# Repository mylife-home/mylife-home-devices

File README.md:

# mylife-home-devices
MyLife Home devices

- [ePanel IO](epanel-io/README.md) :white_check_mark: Module de tableau électrique pour interconnecter E/S avec domotique (rpi/esp)
- [ePanel Energy Monitor](epanel-energy-monitor/README.md) :white_check_mark: Module de tableau électrique pour mesurer la consommation électrique
- [ePanel Controller](epanel-controller/README.md) :white_check_mark: Module de tableau électrique pour contrôler IO et Energy Monitor
- [Garden box](garden-box/README.md) :white_check_mark: Boîtier de commandes/capteurs dans le jardin
- [RGB garden box](rgb-garden-box/README.md) :white_check_mark: Boîtier de commande spots RGB dans le jardin
- [RGB spot 10W](rgb-spot-10w/README.md) :white_check_mark: Reprise de spots existant infrarouge pour connexion direct cables RGB
- [Garage door driver](garage-door-driver/README.md) :white_check_mark: Pilote de porte de garage
- [Clim driver](clim-driver/README.md) :white_check_mark: Pilote de clim
- [Gate driver](gate-driver/README.md) :hourglass: Pilote de portail
- [Bed Smart Plug](bed-smart-plug/README.md) :white_check_mark: "Multiprise intelligente" pour mettre en tête de lit
- [Presence Wifi sensor](presence-wifi-sensor/README.md) :question: Détecteur de présence Wifi
- [RGB LED inverter](rgb-led-inverter/README.md) :no_entry: common anode -> common cathode
- RGB indoor box :question: Boîtier de commande spots/ruban leds RGB en intérieur
- Kitchen hood driver :question: Pilote de hôte
- [Pergola driver](pergola-driver/README.md) :question: Pilote de pergola
- [Fairy lights](fairy-lights/README.md): :white_check_mark: guirlande de noël
- [Heater driver](heater-driver/README.md): :question: pilote de radiateur
- [Deco light](deco-light/README.md): :question: Lumière de décoration

## Notes
- Tutorial KiCad: https://www.youtube.com/playlist?list=PLuQznwVAhY2WA4CIf3_aB_e8hRCSbQuUp
- Best practice routing PCB: https://resources.altium.com/fr/p/top-5-pcb-design-guidelines-every-pcb-designer-needs-know
- Kicad to JLCPCB
  - https://support.jlcpcb.com/article/149-how-to-generate-gerber-and-drill-files-in-kicad
  - https://support.jlcpcb.com/article/84-how-to-generate-the-bom-and-centroid-file-from-kicad
  - plugin pour aide a la generation de commande : https://github.com/Bouni/kicad-jlcpcb-tools
  - plugin pour importer les composants JLCPCB dans Kicad : https://github.com/TousstNicolas/JLC2KiCad_lib
- Component footprints : https://componentsearchengine.com/
- ESP32-POE:
  - NE PAS utiliser GPIO0 si possible (ne pas le mettre DOWN au boot)
  - Attention : Version avec antenne interne est plus grande (pas que l'ESP, toute la board). Le footprint Kicad courant correspond à la version avec antenne externe : 
- ESP8266 strapping pins:
  - GPIO0, GPIO1, GPIO2: boot failure if pulled LOW
  - GPIO15: boot failure if pulled HIGH
  - GPIO1, GPIO2, GPIO3, GPIO9, GPIO10, GPIO16: pin is high at BOOT

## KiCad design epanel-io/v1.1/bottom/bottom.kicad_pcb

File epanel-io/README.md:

# ePanel IO

## Besoin

- 20 IO au moins
- mettre un Switch ou jumper pour relier les phases et neutres de 2 entrées sorties voisines (pour pouvoir relier ensemble ceux qui viennent du même disjoncteur)

- IO / disjoncteurs:
  - R1: 7 + 3 extension + escalier
  - RDC: 5 + porche
  - Dehors: terrasse (vers spa)

## Design

- Rpi pico: 2 modules with 10 I/O each with io port0 = Zc + power supply
- Rpi pico + esp : jumper pour alim séparée => permet live debug usb + reboot ?
- Borniers "détachables" ?
- Noter sur le silkscreen a quoi correspondent les borniers/pin headers/jumpers
- Grouper les IO 4 par 4 (1 phase et 1 neutre pour 4 IO) => 4 + 4 + 2 par RPI

### Materiel

- Boîtier : https://fr.rs-online.com/web/p/boitiers-rail-din/7495837
- Borniers :
  - 2 contacts : https://fr.rs-online.com/web/p/borniers-pour-circuits-imprimes/1444286
  - 3 contacts : https://fr.rs-online.com/web/p/borniers-pour-circuits-imprimes/1444293

---

- Découpage IO:
  - R1: 11     => 4 + 4 + 4
  - RDC: 6     => 4 + 2
  - Dehors: 1  => 2
=> 2x 4+4+2 OK

### ePanel (common with energy monitor)

- i2c bus
- Connexion i2c + power
- master controler olimex esp32 dans le tableau electrique

## V1.1

### Materiel :

- Boitier aéré :
  - CNMB/6V/2 https://fr.rs-online.com/web/p/boitiers-rail-din/7495913
  - CNMB/6V/KIT https://fr.rs-online.com/web/p/boitiers-rail-din/7495840
- Borniers enfichables :
  - Bornier 3 voies : https://fr.farnell.com/phoenix-contact/1792252/fiche-male-90deg-ci-3v-5-08mm/dp/3705456
  - Base 3 voies : https://fr.farnell.com/en-FR/phoenix-contact/mstb-2-5-3-g-5-08/terminal-block-header-3pos-r-a/dp/2671262
  - Bornier 5 voies : https://fr.farnell.com/phoenix-contact/1792278/fiche-male-90deg-ci-5v-5-08mm/dp/3705470
  - Base 5 voies : https://fr.farnell.com/phoenix-contact/1759046/bornier-header-5-voies-90-traversant/dp/2671264

### Observations V1 19 Juillet 2025 sur V1

**Très chauds :**
- R2 - R3
- U2

**Chauds (tout le haut) :**
- U4 R7 et toute la ligne
- R36 diode 1N4007 et toute la ligne

## V1

_Mise en service : 8 OCT 2022_

### Wiring

IO from left to right:  
0,1,2,3, 8,9, 4,5,6,7  
_ZC sur 8,9_

### Top

### Bottom

### Images

#### Fabrication

- enlever les renforts au milieu a la pince + finition dremel
- raboter les cales pour la carte superieure au dremel
- souder les pin headers
- souder les borniers
- couper a la pince les pins qui depassent des soudures de borniers qui empechent de fermer le boitier correctement

_Après fix (Q3/Q4 et Q5/Q6 etaient morts)_

#### Installation

_Ancienne domotique_

_Nouvelle domotique_

## Prototype-1

### Tests

- Code:
  - https://github.com/vincent-tr/pico-experiments/tree/main/zc
  - https://github.com/vincent-tr/pico-experiments/tree/main/triac
  - https://github.com/vincent-tr/pico-experiments/tree/main/mosfet
- Images:
  <br/>

### Observations

- Trous pour borniers trop gros
- Triac:
  - fait clignoter un spot led 10w en OFF
  - fait un leger bruit sur passage de OFF a ON
  - dimming: fait un bourdonnement marqué avec spot 35W (testé à 50/255 et 150/255)
- Mosfet:
  - fait clignoter un spot led 10w en OFF
  - avec resistances 100k en // de la charge, pareil
  - avec spot 35W, R5 brule
  - après avoir changé alim par HLK-PM12, c'est OK!

## Prototype-2

### Tests
- Code:
  - https://github.com/vincent-tr/pico-experiments/tree/main/mosfet
- Images:
  <br/>

### Observations

- Montage faux : j'ai dessoudé la diode D3 et connecté son anode au neutral
- Anoter les IO (dominos/pin headers) sinon c'est difficile a retrouver après
- La taille du PCB correspond parfaitement au boitier DIN : CNMB/4/kit
- Montage fonctionne avec spot 35w + sport réel salon (mais pas avec spot test 10w, que on/off, non dimmable?)
- Pas de chauffe
- pico "RUN" pin si utilisé sur breadboard doit être relié au VCC, sinon le laisser dangling peut causer des reboot intempestifs

## Prototype-3

### Tests

- Images:
  <br/>

## Notes

### Mosfet dimmer schematics

- [Prototype1 (does not work)](mosfet-dimmer.png)
- https://electronics.stackexchange.com/questions/557763/trailing-edge-dimmer-circuit-limitations
- https://sound-au.com/project157.htm
- https://electronics.stackexchange.com/questions/277884/problems-with-a-back-to-back-mosfet-dimmer-for-230vac
- IRF740 -> 10A

### 220v current sensor (input)

- https://arduino.stackexchange.com/questions/37044/127v-220v-ac-sensor-whats-the-role-of-this-particular-resistor
- https://smartsolutions4home.com/detecting-mains-voltage-with-microcontroller/
- https://bytesofgigabytes.com/embedded/sensing-ac-voltage-using-microcontroller/
- Zc : https://electronics.stackexchange.com/questions/215094/how-to-test-if-zero-crossing-is-working

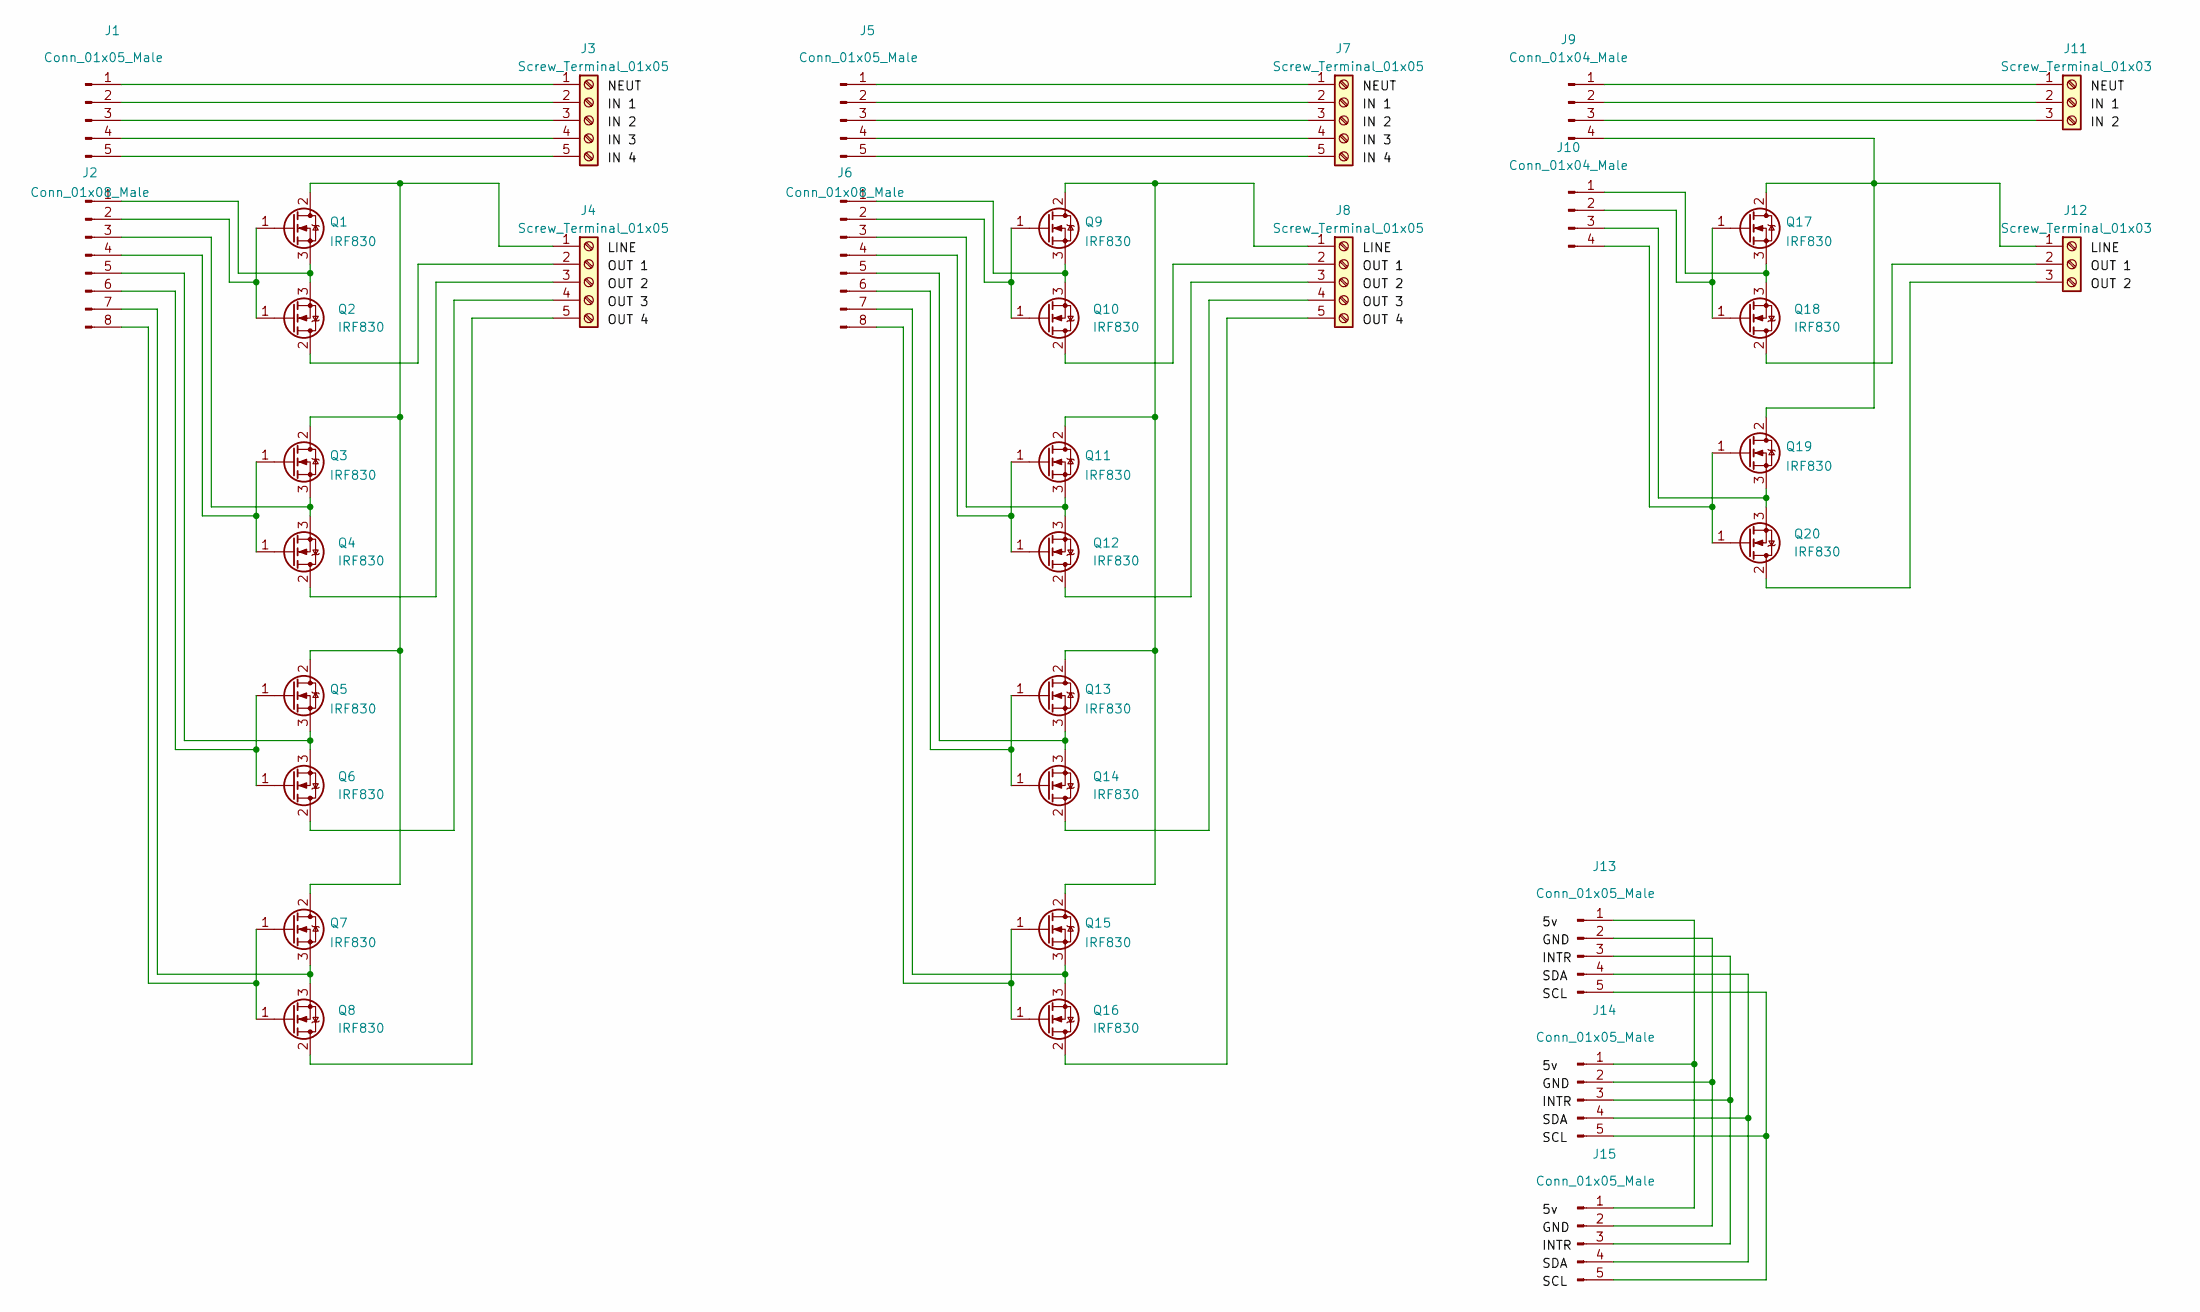
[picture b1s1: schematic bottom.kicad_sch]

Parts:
J1, J5, J13, J14, J15: Conn_01x05_Male; PinHeader_1x05_P2.54mm_Vertical
J2, J6: Conn_01x08_Male; PinHeader_1x08_P2.54mm_Vertical
J3, J4, J7, J8: Screw_Terminal_01x05; TerminalBlock_bornier-5_P5.08mm
J9, J10: Conn_01x04_Male; PinHeader_1x04_P2.54mm_Vertical
J11, J12: Screw_Terminal_01x03; TerminalBlock_bornier-3_P5.08mm
Q1, Q2, Q3, Q4, Q5, Q6, Q7, Q8, Q9, Q10, Q11, Q12, Q13, Q14, Q15, Q16, Q17, Q18, Q19, Q20: IRF830; TO-263-3_TabPin2; LCSC C693297

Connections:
unnamed: J1.1, J3.1
unnamed: J1.2, J3.2
unnamed: J1.3, J3.3
unnamed: J1.4, J3.4
unnamed: J1.5, J3.5
unnamed: J2.1, Q1.3 (S), Q2.3 (S)
unnamed: J2.2, Q1.1 (G), Q2.1 (G)
unnamed: J2.3, Q3.3 (S), Q4.3 (S)
unnamed: J2.4, Q3.1 (G), Q4.1 (G)
unnamed: J2.5, Q5.3 (S), Q6.3 (S)
unnamed: J2.6, Q5.1 (G), Q6.1 (G)
unnamed: J2.7, Q7.3 (S), Q8.3 (S)
unnamed: J2.8, Q7.1 (G), Q8.1 (G)
unnamed: J4.1, Q1.2 (D), Q3.2 (D), Q5.2 (D), Q7.2 (D)
unnamed: J4.2, Q2.2 (D)
unnamed: J4.3, Q4.2 (D)
unnamed: J4.4, Q6.2 (D)
unnamed: J4.5, Q8.2 (D)
unnamed: J5.1, J7.1
unnamed: J5.2, J7.2
unnamed: J5.3, J7.3
unnamed: J5.4, J7.4
unnamed: J5.5, J7.5
unnamed: J6.1, Q9.3 (S), Q10.3 (S)
unnamed: J6.2, Q9.1 (G), Q10.1 (G)
unnamed: J6.3, Q11.3 (S), Q12.3 (S)
unnamed: J6.4, Q11.1 (G), Q12.1 (G)
unnamed: J6.5, Q13.3 (S), Q14.3 (S)
unnamed: J6.6, Q13.1 (G), Q14.1 (G)
unnamed: J6.7, Q15.3 (S), Q16.3 (S)
unnamed: J6.8, Q15.1 (G), Q16.1 (G)
unnamed: J8.1, Q9.2 (D), Q11.2 (D), Q13.2 (D), Q15.2 (D)
unnamed: J8.2, Q10.2 (D)
unnamed: J8.3, Q12.2 (D)
unnamed: J8.4, Q14.2 (D)
unnamed: J8.5, Q16.2 (D)
unnamed: J10.1, Q17.3 (S), Q18.3 (S)
unnamed: J10.2, Q17.1 (G), Q18.1 (G)
unnamed: J10.3, Q19.3 (S), Q20.3 (S)
unnamed: J10.4, Q19.1 (G), Q20.1 (G)
unnamed: J9.1, J11.1
unnamed: J9.2, J11.2
unnamed: J9.3, J11.3
unnamed: J9.4, J12.1, Q17.2 (D), Q19.2 (D)
unnamed: J12.2, Q18.2 (D)
unnamed: J12.3, Q20.2 (D)
unnamed: J13.1, J14.1, J15.1
unnamed: J13.2, J14.2, J15.2
unnamed: J13.3, J14.3, J15.3
unnamed: J13.4, J14.4, J15.4
unnamed: J13.5, J14.5, J15.5

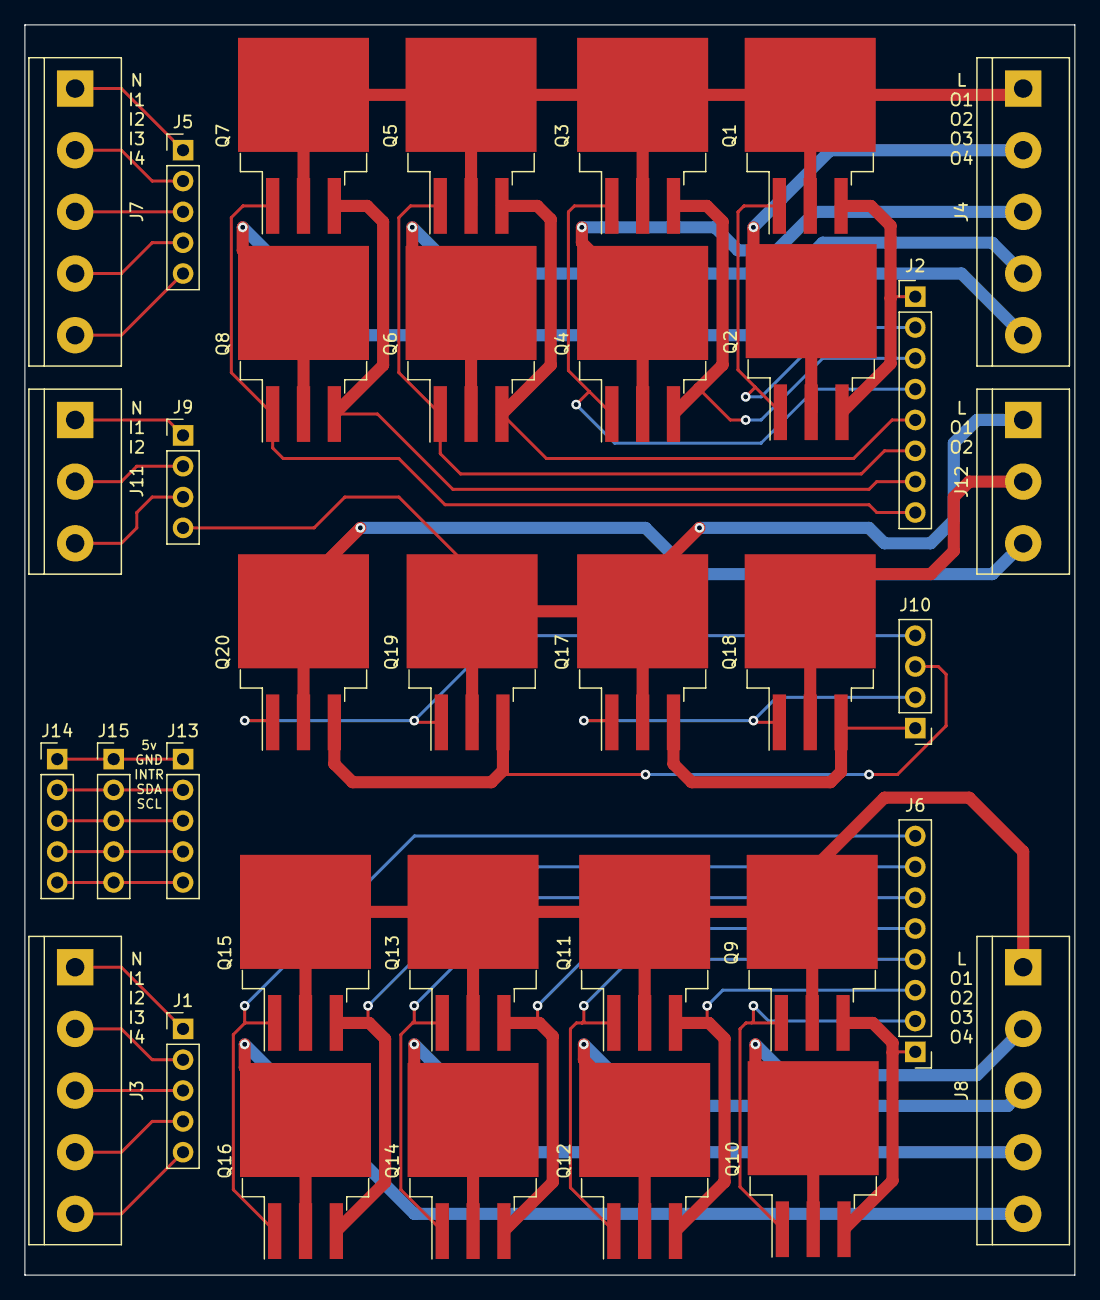
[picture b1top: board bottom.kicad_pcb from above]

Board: 2 copper layers, 86.5 x 103.0 mm, 35 parts (0 on the bottom side), 51 nets.

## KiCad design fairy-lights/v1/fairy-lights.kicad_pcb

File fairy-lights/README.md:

# Fairy lights

## Besoin

- Avec Eléonore
- Guirlande pour sapin
- Intégré ESPHome

## Design

- Guirlande :
  - WS2812B
  - https://amzn.eu/d/6PvWFXF
  - ( https://www.adafruit.com/product/4917 )
- Contrôleur :
  - WeMos D1 mini, sur gpio3 pour DMA
  - config esphome dma -> GPIO3 - RX
- Alimentation :
  - Puissance guirlande : Alim 5V 6A -> 60ma / led
  - ~alim 6A (69.5x39x24) : https://fr.rs-online.com/web/p/alimentations-a-decoupage/1358945~
  - ~alim 8A (87x52x29.5) : https://fr.rs-online.com/web/p/alimentations-a-decoupage/1358955~
  - alime externe 5V 8A : https://www.amazon.fr/dp/B088FBXTPS : `+` au milieu `-` à l'extérieur, 5.5mm - 2.5mm
  - Connecteur : 
    - https://fr.rs-online.com/web/p/connecteurs-d-alimentation-dc/2832406 - 283-2406
    - ( https://fr.rs-online.com/web/p/connecteurs-d-alimentation-dc/8782606 )
- IRLZ44N pour switch l'alim (sans heatsink), sortie esp direct sur Din LEDs : https://fr.rs-online.com/web/p/transistors-mosfet/5410086 541-0086
- Boitier : https://fr.rs-online.com/web/p/boitiers-pour-usage-general/9190373 - 919-0373

## V1

### Wiring

- `+` -> fil avec points noirs
- `D` -> fil du milieu
- `-` -> fil de l'autre côté 

### 3D view

### Main

### Images

## Prototype 1

- Sur breadboard
- Verifier qu'on peut piloter la guirlande avec esp8366/esphome

### Pinout de la guirlande

- `+` -> fil avec points noirs
- `D` -> fil du milieu
- `-` -> fil de l'autre côté

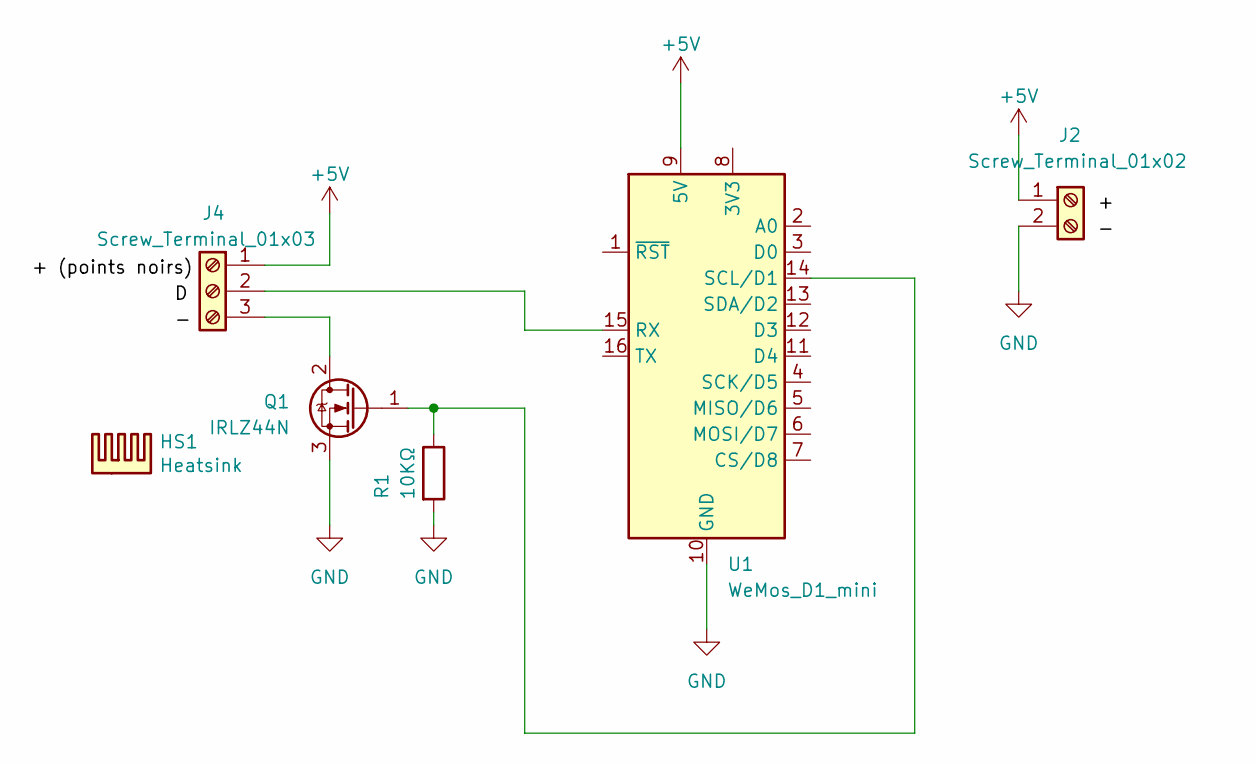
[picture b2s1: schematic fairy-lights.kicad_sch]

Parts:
HS1: Heatsink; Heatsink_Fischer_SK104-STC-STIC_35x13mm_2xDrill2.5mm
J2: Screw_Terminal_01x02; TerminalBlock_bornier-2_P5.08mm
J4: Screw_Terminal_01x03; TerminalBlock_bornier-3_P5.08mm
Q1: IRLZ44N; TO-220-3_Vertical
R1: 10KΩ; R_Axial_DIN0207_L6.3mm_D2.5mm_P15.24mm_Horizontal
U1: WeMos_D1_mini; WEMOS_D1_mini_light

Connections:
+5V: J2.1, J4.1, U1.9 (5V)
GND: J2.2, Q1.3 (S), R1.2, U1.10 (GND)
unnamed: J4.2, U1.15 (RX)
unnamed: J4.3, Q1.2 (D)
unnamed: Q1.1 (G), R1.1, U1.14 (SCL/D1)

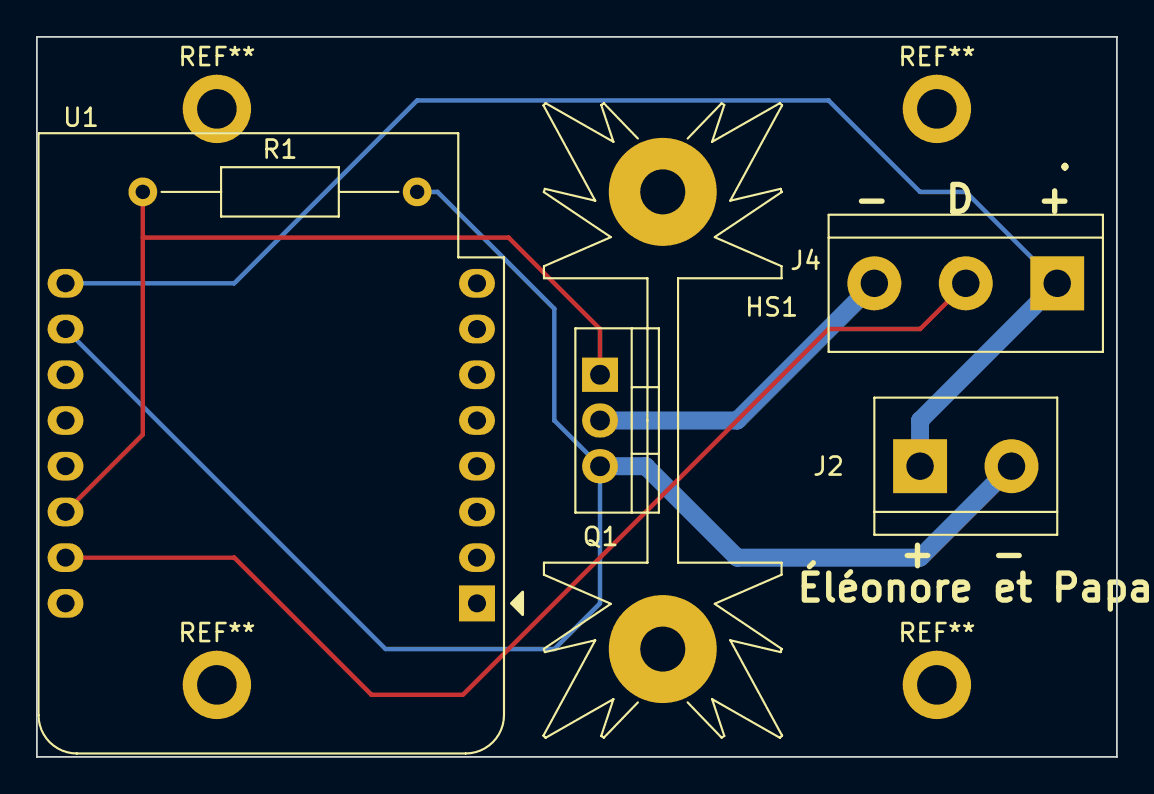
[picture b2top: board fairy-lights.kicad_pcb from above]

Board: 2 copper layers, 60.0 x 40.0 mm, 6 parts (0 on the bottom side), 5 nets.

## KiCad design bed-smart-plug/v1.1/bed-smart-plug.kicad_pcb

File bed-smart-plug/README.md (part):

# Bed Smart Plug

## Besoin

- Récepteur 433mhz (pour télécommande)
- Capteur température
- 4 sorties prises entre 5W et 200W
- Wifi et Ethernet
- Boitier :
  - peut etre relativement large/long, mais plat
  - avec les prises sur un côté
  - comme un switch
  - comme ca on peut le mettre sous un meuble, ou derriere un meuble debout

### Emplacements

- chambre parents
- chambre Eléonore
- chambre Éloïse
- chambre d'amis ?
- rdc derrière TV ?
- bibliothèque pour lampe pot de fleurs + température ?

## Choix techniques

- ESP32 ethernet ou wifi
  - prévoir des trous sur le PCB pour fixer l'esp avec un serre flex entre son header et son module ESP, sur l'inscription "ESP32-PoE"
- SSR pour éviter claquement relais
  - BT136 (4A max)
  - Dissipateurs
  - Fusible 5x20 à souder
- Entree Prise alim IEC C14
- Sorties prises IEC C13 pour avoir un format plus compact
- Capteur température :
  - DS18b20
  - avec Jack
  - possible souder jack a la main sinon
  - capteur integré inutile (mesure la temperature de l'esp/des triac pas de la piece)
- Télécommande 433MHz:
  - Renkforce 1208459
  - https://amzn.eu/d/fGBrWJP
  - https://www.conrad.fr/fr/p/renkforce-1208459-sans-fil-telecommande-interieure-1208459.html

## Design

- Board : ESP32-POE https://www.olimex.com/Products/IoT/ESP32/ESP32-POE/open-source-hardware
- Alim 220v -> 5V 1A : 
  - ~~https://fr.rs-online.com/web/p/alimentations-a-decoupage/1812200~~ (n'existe plus)
  - https://fr.rs-online.com/web/p/alimentations-a-decoupage/1359226
- Jack DS18B20 :
  - https://www.amazon.fr/dp/B075FYYLLV/
  - https://fr.rs-online.com/web/p/connecteurs-jacks/5051299
- Récepteur 433MHz : (modulation ASK)
  - ~~AM-RX12A-433P https://fr.farnell.com/rf-solutions/am-rx12a-433p/recepteur-module-rf-433-92-110dbm/dp/2759279~~ (frais de gestion trop chers)
  - QAM-RX10-433 https://fr.rs-online.com/web/p/modules-rf/1258208
  - pinout compatible
  - normalement 5V, tester en broadboard avec alim 5V + pont diviseur sur les data pour passer a 3.3V
- Triac : BT136-600E https://fr.rs-online.com/web/p/triac/7271120
  - ~~Dissipateur https://fr.rs-online.com/web/p/dissipateurs-de-chaleur/1898101/~~
  - moins haut, même base : https://fr.rs-online.com/web/p/dissipateurs-de-chaleur/1898094
  - vis M3 : même que garden box : https://fr.rs-online.com/web/p/vis-a-rondelle-indesserrable/0279149
  - écrous M3 : https://fr.rs-online.com/web/p/ecrous-hexagonaux/0560293
- Porte fusible : https://fr.rs-online.com/web/p/porte-fusibles/1769047
  - Fusible : https://fr.rs-online.com/web/p/fusibles-cartouches/6686007
- Boitier :
  - https://fr.rs-online.com/web/p/boitiers-pour-usage-general/8180494
    - noir comme les connecteurs C13/C14
    - les facades laterales sont d'un seul tenant: le couvercle est "plat", plus facile pour percer les facades.
  - Vis de fixation PCB : https://fr.rs-online.com/web/p/vis-autotaraudeuses/4831202
- Prises :
  - ~~entree C14 : https://fr.rs-online.com/web/p/connecteurs-iec/8117207~~
  - ~~sortie C13 : https://fr.rs-online.com/web/p/connecteurs-iec/8117193~~
  - sortie C13 x 4 à clip : https://fr.rs-online.com/web/p/connecteurs-iec/2318101
    - couper une barre (phase), laisser les 2 autres
    - montage :

  - entrée C13 à clip : https://fr.rs-online.com/web/p/connecteurs-iec/0481623
    - montage :

  - ~~1 entrée 4 sorties : https://fr.rs-online.com/web/p/connecteurs-iec/3135474~~
    - semble indisponible

  - Prise C14 pour câbles : https://amzn.eu/d/47d2yMY

## Observations Prototype-1 epanel-io

- cf [epanel-io/README.md#observations](../epanel-io/README.md#observations) - Triac
- si on enleve snubber du phototriac, toujours une fuite (couper la piste entre C3 et C4)
- si on enleve les 2 snubbers, plus de fuite, spot led 10w reste eteint (couper la piste entre C3 et le triac)

## Prototype-1

### Objectifs

- Triac: 
  - dissipateurs
  - snubbers/bruit/fuite
    - spot 10w
    - guirlande boules
    - lampe bureau
    - lampe chevet
    - alim a decoupage
- 433MHz receiver
  - binding avec telecommandes
- ds18b20
  - jack pinout: voir quelles broches sur chaque prise matchent + selectionner le pinout qu'on veut.
- fusibles

### Schematic

- [Schematic](prototype-1/schematic.png)

### Pinout

- GPIO02 : Triac
- GPIO13 : DS18B20
- GPIO36 : Récepteur 433MHz

### Observations

- Dissipateur :
  - Rapprocher dissipateur et triac de 0.5 - 1 mm
  - Fixation dissipateur/triac : écrou M3 + reprendre vis M3 anti-deserrage garden-box
- Fusibles : OK
- Triac :
  - spot 10w :
    - triac snubber => fuite (KO)
    - opto snubber => fuite (KO)
    - sans snubber => pas de bruit (OK)
  - Perceuse à colonne :
    - puissance : 1.6A au démarrage puis 0.8
    - Avec/Sans snubber : pas de bruit mais la perceuse fait elle du bruit
    - apres 5 mins dissipateur + triac froids 
  - Lampe chevet Éloïse
    - puissance : 26.5ma
    - Avec snubber : KO bruit quand off
    - Sans snubber : OK sans bruit
  - Guirlande Éloïse
    - Avec snubber : KO clignote
    - Sans snubber : OK sans bruit
    - puissance très instable semble avec des pics a 600ma puis revient a 0ma (problème multimètre ?)
  - Lampe bureau
    - puissance semble 25ma (problème multimètre ?)
    - Avec snubber : KO bruit quand off
    - Sans snubber : OK sans bruit
  - Lampe chevet Eléonore
    - puissance 1.5a???? (problème multimètre ?) -> Ampoule à incandescence 40W
    - Avec snubber : OK sans bruit
    - Sans snubber : OK sans bruit
- Prise jack 

  (de gauche à droite) 
  - 1 : corps
  - 2 : pin penché 
  - 3 : base pin central
  - 4 : extrémité pin central

  Attention : bien enfoncer la prise
  - On peut mettre la prise sous l'ESP

- Récepteur 433mhz
  - Les 2 pins data sont reliés ensemble 
  - Connecter au 5V, et mettre un point diviseur :
    - R1 = 10k (entre output recepteur et input ESP)
    - R2 = 2x 10k en série (entre input ESP et GND)
  - Config dump : 
```yaml
    remote_receiver:
      pin: GPIO36
      dump:
      - rc_switch
      tolerance: 50%
      filter: 250us
      idle: 4ms
      buffer_size: 2kb
```
  - Valeurs (le repeat est très rapproché) : 
    - `Received RCSwitch Raw: protocol=1 data='...'`
  
  _Config télécommande grise : 1 = ON, 5 = ON_
  
| Action | code télécommande | code ABCD | ?? | on/off |
|---|---|---|---|---|
| A on   | 00 01 01 01 00 | 00 01 01 01 | 01 | 00 01 |
| A off  | 00 01 01 01 00 | 00 01 01 01 | 01 | 01 00 |
| B on   | 00 01 01 01 00 | 01 00 01 01 | 01 | 00 01 |
| B off  | 00 01 01 01 00 | 01 00 01 01 | 01 | 01 00 |
| C on   | 00 01 01 01 00 | 01 01 00 01 | 01 | 00 01 |
| C off  | 00 01 01 01 00 | 01 01 00 01 | 01 | 01 00 |
| D on   | 00 01 01 01 00 | 01 01 01 00 | 01 | 00 01 |
| D off  | 00 01 01 01 00 | 01 01 01 00 | 01 | 01 00 |

  _Config télécommande blanche : 1 = ON, 2 = ON_

  => Code télécommande : `00 00 01 01 01`, le reste semble correspondre

  - Avec récepteur dans salon :
    - Fontionne depuis CH1
    - Fonctionne depuis CHP

  _Config télécommande renkforce : pos 1_

| Action | code télécommande | code ABCD | ?? | on/off |
|---|---|---|---|---|
| 1 on   | 00 01 01 01 | 00 01 01 01 01 | 01 | 01 01 |
| 1 off  | 00 01 01 01 | 00 01 01 01 01 | 01 | 01 00 |
| 2 on   | 00 01 01 01 | 01 00 01 01 01 | 01 | 01 01 |
| 2 off  | 00 01 01 01 | 01 00 01 01 01 | 01 | 01 00 |
| 3 on   | 00 01 01 01 | 01 01 00 01 01 | 01 | 01 01 |
| 3 off  | 00 01 01 01 | 01 01 00 01 01 | 01 | 01 00 |
| 4 on   | 00 01 01 01 | 01 01 01 00 01 | 01 | 01 01 |
| 4 off  | 00 01 01 01 | 01 01 01 00 01 | 01 | 01 00 |

## Prototype-2

### Objectifs

- boitier 
- sortie RJ45
- sortie prise jack
- fixations C13/C14
- tester nouveau dissipateur

### Observations

- Dissipateur + écrou de fixation OK
- Boîtier :
  - pas assez long (on ne peut pas mettre toutes les prises + ESP)
  - pas assez large (ESP ne tient pas en largeur)
  - hauteur OK mais prise C14 avec vis sur les côtés ne tient pas en hauteur : voir pour prendre une encastrable comme la multiprise C13
  - aluminium pour ne pas se déformer avec les trous ?
  - aérations ?
  - **aluminium trop cher, autres boitiers mauvaise taille. On garde celui là mais en mettant l'alime/jack/rj45 sur un côté**
- Multiprise C13 x4 : séparation des phases OK

- Perçage boitier pour multiprise C13x4
  - Tracer au cutter + règle métallique
  - Le gros :
    - Découpage disque Dremel vitesse 5 + coins avec perceuse a colonne plus gros forêt placo (faire coins en premier)
  - la finition :
    - tubes ponceuse Dremel, vitesse 2.5
    - gros tube pour partie plate + coins arrondis
    - petit tube pour coin moins arrondis (cf forme des prises)
    - lime pour égaliser
  - Passage des clips (le boitier est trop épais)
    - Entamer l'épaisseur avec gros tube
    - Installation de la prise : pousser les clips vers l'extérieur depuis l'intérieur des prises

  - Tests:
    - branchement/debranchement prise OK
    - on peut manoeuvrer les clips depuis l'intérieur des prises pour démonter la multiprise après installation
    - vue de haut, empreinte des prises sur le CI = 110x30
- Vis de fixation PCB OK

## Proto 3

### Objectifs

- Taille CI dans boitier
- Emplacement ESP32 pour sortie RJ45
- Emplacement Jack pour sortie boitier -> elle doit passer sous RJ45
- Est-ce que le PCB peut passer sous les prises ?
  -> oui sous prise alim (plus petite que sorties)
  -> essayer de mettre prise alim a côté de prises sorties
  -> faire un PCB qui ne passe pas sous prises sorties (inutile)

Abandonné car gros cher vs V1

Prix proto : 
- build : 19.20
- total : ~45eur

Prix v1 :
- build : 43.06
- total : ~70eur

## V1 (KO)

### Observations

- Pinout Récepteur 433MHz mauvais : trou pas au bon endroit (decaler vers le bas) + trous trop petits (reprendre ceux de l'ESP)
- Encoches angles PCB trop petits, refaire les coins un carré de 10mm de côté
  => deplacer le dissipateur de gauche
- Trous serre flex ESP OK
- Taille PCB OK
- Vis PCB OK (attention le taraudage use le trou, on ne peut pas visser/devisser 50x)
- Sortie Jack OK, améliorer le placement (faire un gabarit en carton)
- Borniers
  - Gros OK mais trop pret du bord de 2mm
  - Petit OK
- Fusible passe sous prise, attention peu de place
- Sortie RJ45 OK
- Prise alim OK
- On peut mettre/enlever l'ESPESP quand la carte est vissée (le serre-flex semble même superflu, on peut le laisser quand même par sécurité)
- Notes :
  - Utiliser avant dernier forêt placo pour faire les trous des angles
  - Puis utiliser gros puis petite raboteuse granuleuse de Dremel pour les bords droits
  - utiliser toute petite raboteuse métallique pour les finitions

## V1.1

### Wiring

- Pinout jack :
  - Rouage : VCC : bout => 4
  - Noir : GND : sur le corps => 1
  - Jaune : DATA : tige sur le côté => 2-3

### 3D view

### Schematic

### Perçage facades

#### Gabarits

- Entrées

- Sorties

- A imprimer

#### Notes

- Utiliser avant dernier forêt placo pour faire les trous des angles
- Puis utiliser gros puis petite raboteuse granuleuse de Dremel pour les bords droits
- utiliser toute petite raboteuse métallique pour les finitions
- Utiliser plus gros forêt pour la prise jack (le corps de la prise doit passer dedans)

### Correctifs

- mauvaise tension alimentation récepteur 433MHz

  - limer piste alimentation récepteur 433MHz
  - ponter alimentation sur 5V ESP

### Images

## Notes

- Schémas
  - **https://innovatorsguru.com/switching-ac-load-using-triac/**
  - https://www.sonelec-musique.com/electronique_realisations_interfaces_230v_001.html
  - http://www.sper.hr/eng/solid_state_relay_scheme.htm
  - https://fr.rs-online.com/web/p/triac/7142577
  - http://wiring.org.co/learning/basics/lightbulb.html
  - https://www.sonelec-musique.com/electronique_realisations_relais_statique_001.html
  - https://electronics.stackexchange.com/questions/531528/relay-circuit-with-moc3021-and-bt136
  - https://electronics.stackexchange.com/questions/488518/triac-switch-circuit-using-moc3021-and-bt136
  - http://www.farnell.com/datasheets/97984.pdf (fig. 8)
  - Attention a garder le port USB accessible
- triacs
  - comparaison specs : https://www.esr.co.uk/components/products/frame-triacs.htm
- boitier à imprimer
  - fusion 360
  - https://www.thingiverse.com/thing:3700953 (esp32-poe box case, pour la taille + le socket)
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
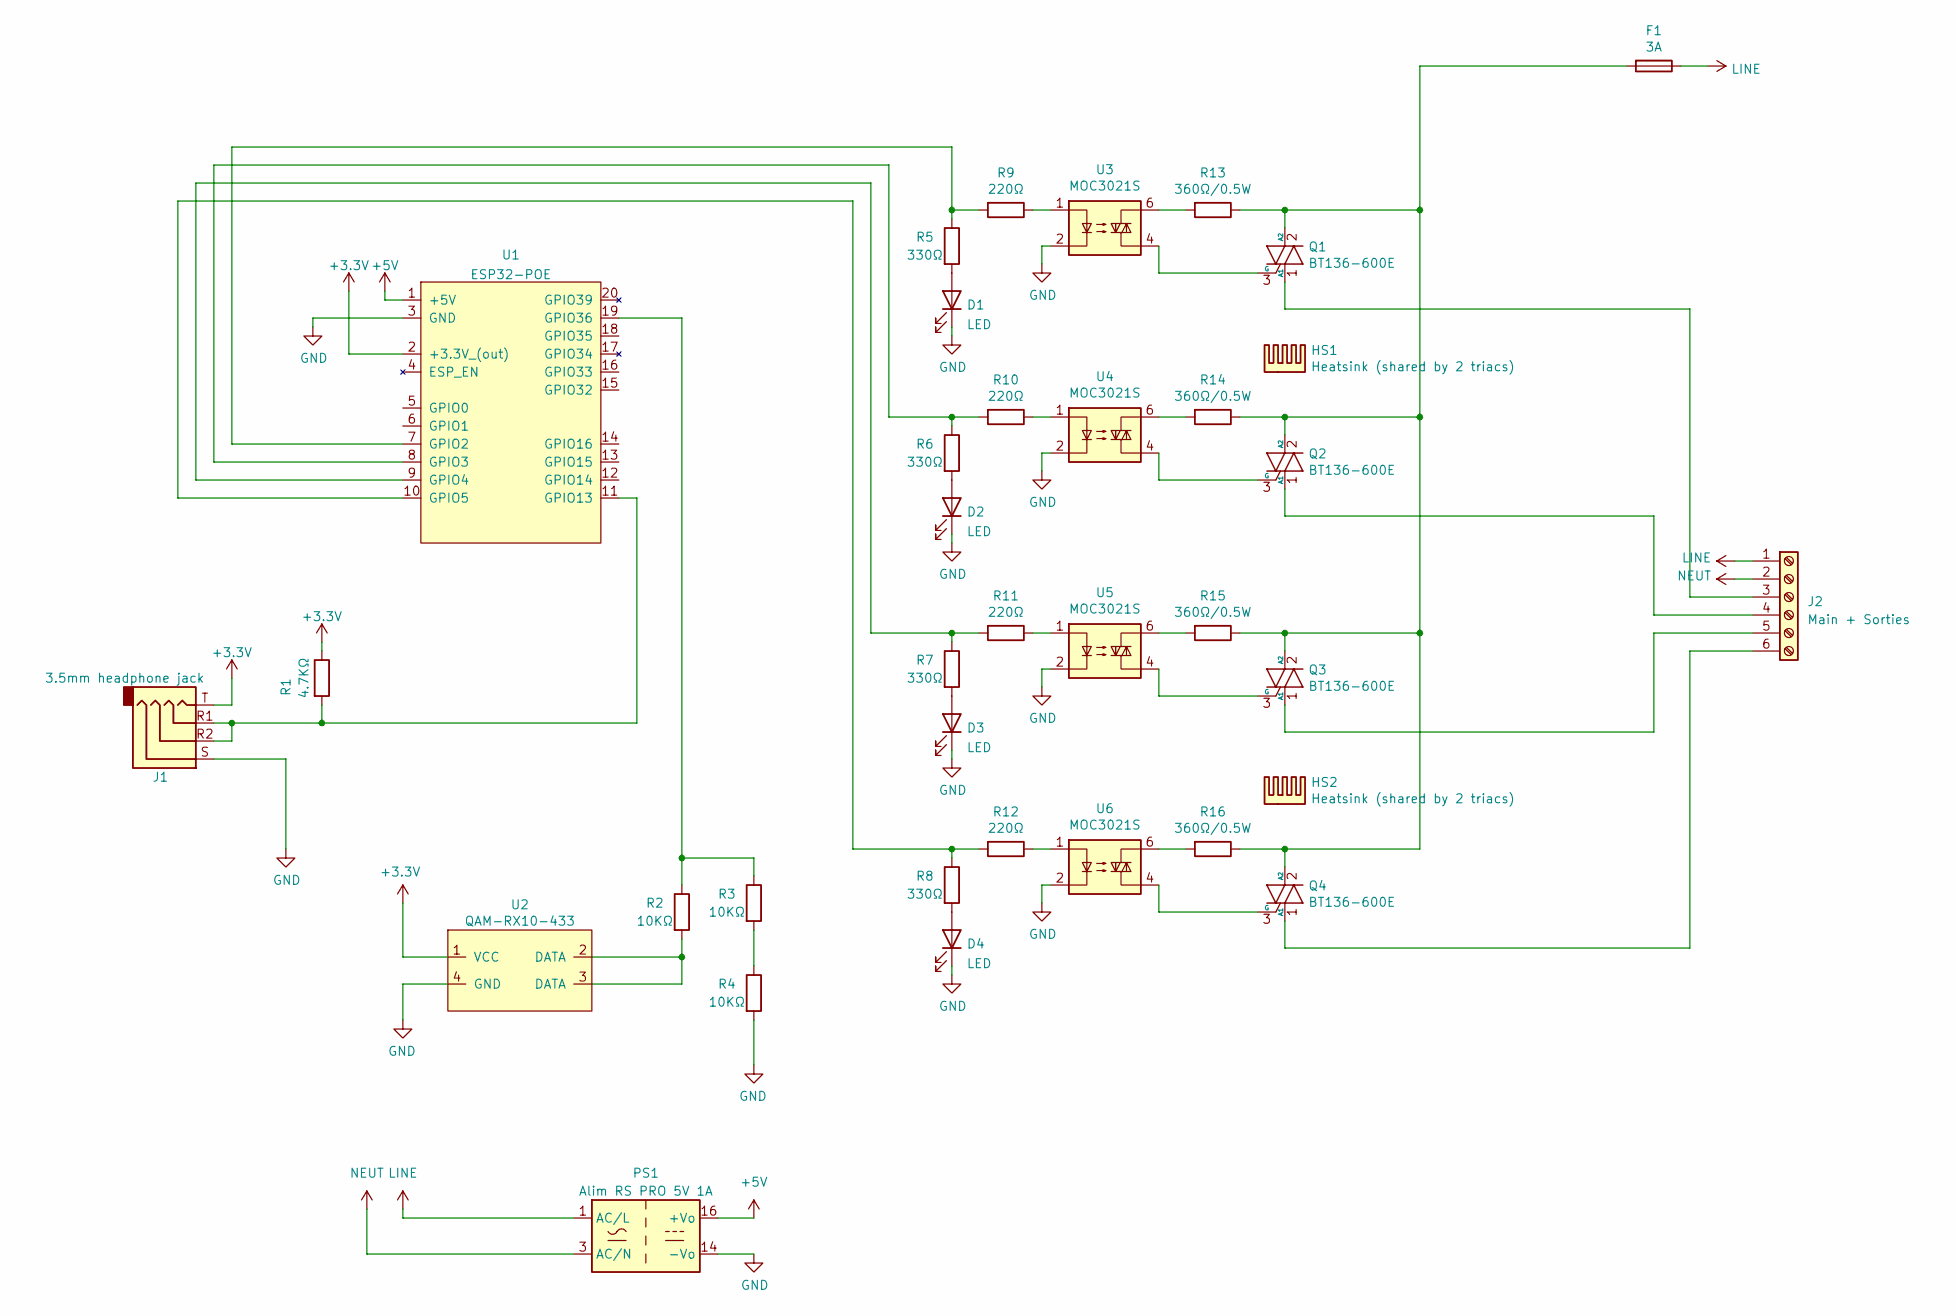
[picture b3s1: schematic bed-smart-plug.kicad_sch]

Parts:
D1, D2, D3, D4: LED; D_0805_2012Metric; LCSC C2297
F1: 3A; Fuseholder_Cylinder-5x20mm_Schurter_0031_8201_Horizontal_Op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
HS1, HS2: Heatsink (shared by 2 triacs); Heatsink_Fischer_SK104-STC-STIC_35x13mm_2xDrill2.5mm
J1: 3.5mm headphone jack; Jack_3.5mm_PJ320D_Horizontal; LCSC C521460
J2: Main + Sorties; TerminalBlock_bornier-6_P5.08mm
PS1: Alim RS PRO 5V 1A; Converter_ACDC_MeanWell_IRM-03-xx_THT
Q1, Q2, Q3, Q4: BT136-600E; TO-220-3_Vertical
R1: 4.7KΩ; R_0402_1005Metric; LCSC C25900
R2, R3, R4: 10KΩ; R_0603_1608Metric; LCSC C4226066
R5, R6, R7, R8: 330Ω; R_0603_1608Metric; LCSC C2918523
R9, R10, R11, R12: 220Ω; R_0603_1608Metric; LCSC C22962
R13, R14, R15, R16: 360Ω/0.5W; R_1210_3225Metric; LCSC C2759574
U1: ESP32-POE
U2: QAM-RX10-433
U3, U4, U5, U6: MOC3021S; SMDIP-6_W9.53mm; LCSC C427436

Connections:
+3V3: J1.T, R1.1, U1.2 (+3.3V_(out)), U2.1 (VCC)
+5V: PS1.16 (+Vo), U1.1 (+5V)
GND: D1.1 (K), D2.1 (K), D3.1 (K), D4.1 (K), J1.S, PS1.14 (-Vo), R4.2, U1.3 (GND), U2.4 (GND), U3.2, U4.2, U5.2, U6.2
LINE: F1.1, J2.1, PS1.1 (AC/L)
NEUT: J2.2, PS1.3 (AC/N)
unnamed: D1.2 (A), R5.2
unnamed: D2.2 (A), R6.2
unnamed: D3.2 (A), R7.2
unnamed: D4.2 (A), R8.2
unnamed: J2.3, Q1.1 (A1)
unnamed: J2.4, Q2.1 (A1)
unnamed: J2.5, Q3.1 (A1)
unnamed: J2.6, Q4.1 (A1)
unnamed: F1.2, Q1.2 (A2), Q2.2 (A2), Q3.2 (A2), Q4.2 (A2), R13.1, R14.1, R15.1, R16.1
unnamed: Q1.3 (G), U3.4
unnamed: Q2.3 (G), U4.4
unnamed: Q3.3 (G), U5.4
unnamed: Q4.3 (G), U6.4
unnamed: R2.2, U2.2 (DATA), U2.3 (DATA)
unnamed: R3.2, R4.1
unnamed: R9.1, U3.1
unnamed: R10.1, U4.1
unnamed: R11.1, U5.1
unnamed: R12.1, U6.1
unnamed: R13.2, U3.6
unnamed: R14.2, U4.6
unnamed: R15.2, U5.6
unnamed: R16.2, U6.6
unnamed: R5.1, R9.2, U1.7 (GPIO2)
unnamed: R6.1, R10.2, U1.8 (GPIO3)
unnamed: R7.1, R11.2, U1.9 (GPIO4)
unnamed: R8.1, R12.2, U1.10 (GPIO5)
unnamed: J1.R1, J1.R2, R1.2, U1.11 (GPIO13)
unnamed: R2.1, R3.1, U1.19 (GPIO36)

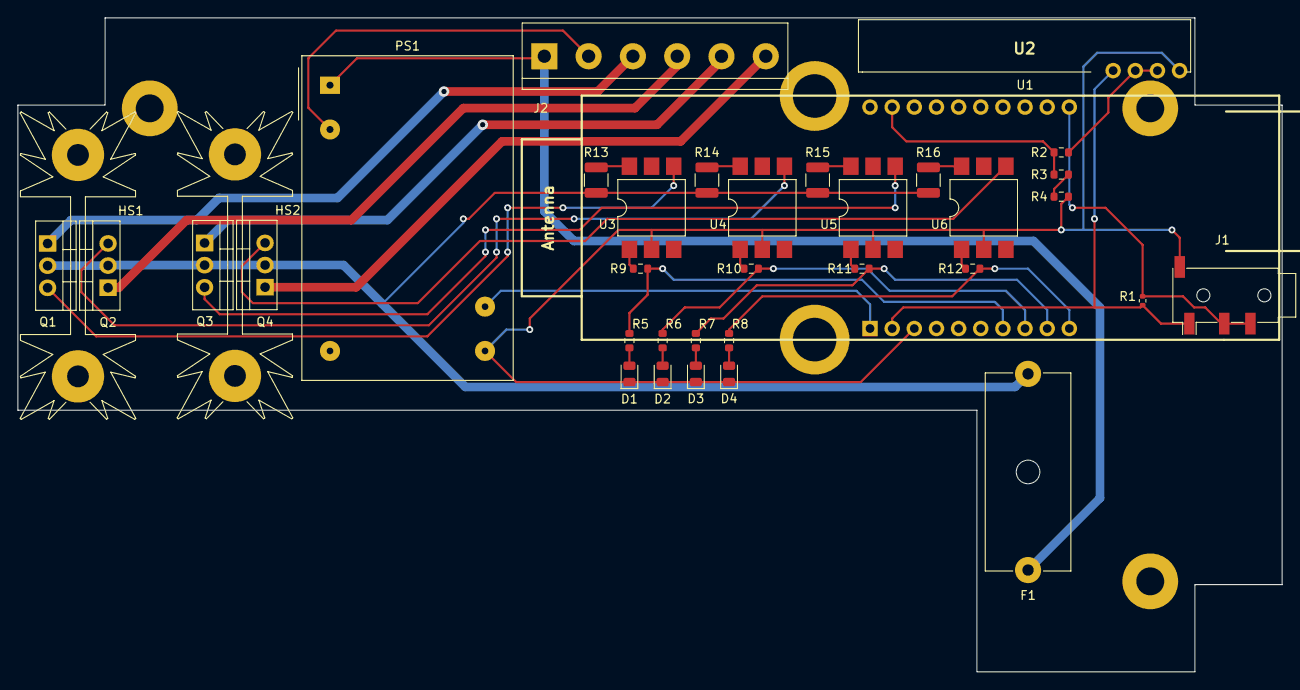
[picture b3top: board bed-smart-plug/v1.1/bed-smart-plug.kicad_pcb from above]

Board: 2 copper layers, 145.0 x 75.0 mm, 36 parts (0 on the bottom side), 34 nets.

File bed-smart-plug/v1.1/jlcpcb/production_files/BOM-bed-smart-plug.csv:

Comment,Designator,Footprint,LCSC
220Ω,"R10,R11,R12,R9",R_0603_1608Metric,C22962
LED,"D1,D2,D3,D4",D_0805_2012Metric,C2297
4.7KΩ,R1,R_0402_1005Metric,C25900
360Ω/0.5W,"R13,R14,R15,R16",R_1210_3225Metric,C2759574
330Ω,"R5,R6,R7,R8",R_0603_1608Metric,C2918523
10KΩ,"R2,R3,R4",R_0603_1608Metric,C4226066
MOC3021S,"U3,U4,U5,U6",SMDIP-6_W9.53mm,C427436
3.5mm headphone jack,J1,Jack_3.5mm_PJ320D_Horizontal,C521460
Main + Sorties,J2,TerminalBlock_bornier-6_P5.08mm,
ESP32-POE,U1,ESP32-POE,
QAM-RX10-433,U2,QAM-RX10-433,
BT136-600E,Q3,TO-220-3_Vertical,
BT136-600E,Q4,TO-220-3_Vertical,
BT136-600E,Q2,TO-220-3_Vertical,
Alim RS PRO 5V 1A,PS1,Converter_ACDC_MeanWell_IRM-03-xx_THT,
Heatsink (shared by 2 triacs),HS1,Heatsink_Fischer_SK104-STC-STIC_35x13mm_2xDrill2.5mm,
BT136-600E,Q1,TO-220-3_Vertical,
Heatsink (shared by 2 triacs),HS2,Heatsink_Fischer_SK104-STC-STIC_35x13mm_2xDrill2.5mm,
3A,F1,Fuseholder_Cylinder-5x20mm_Schurter_0031_8201_Horizontal_Open,

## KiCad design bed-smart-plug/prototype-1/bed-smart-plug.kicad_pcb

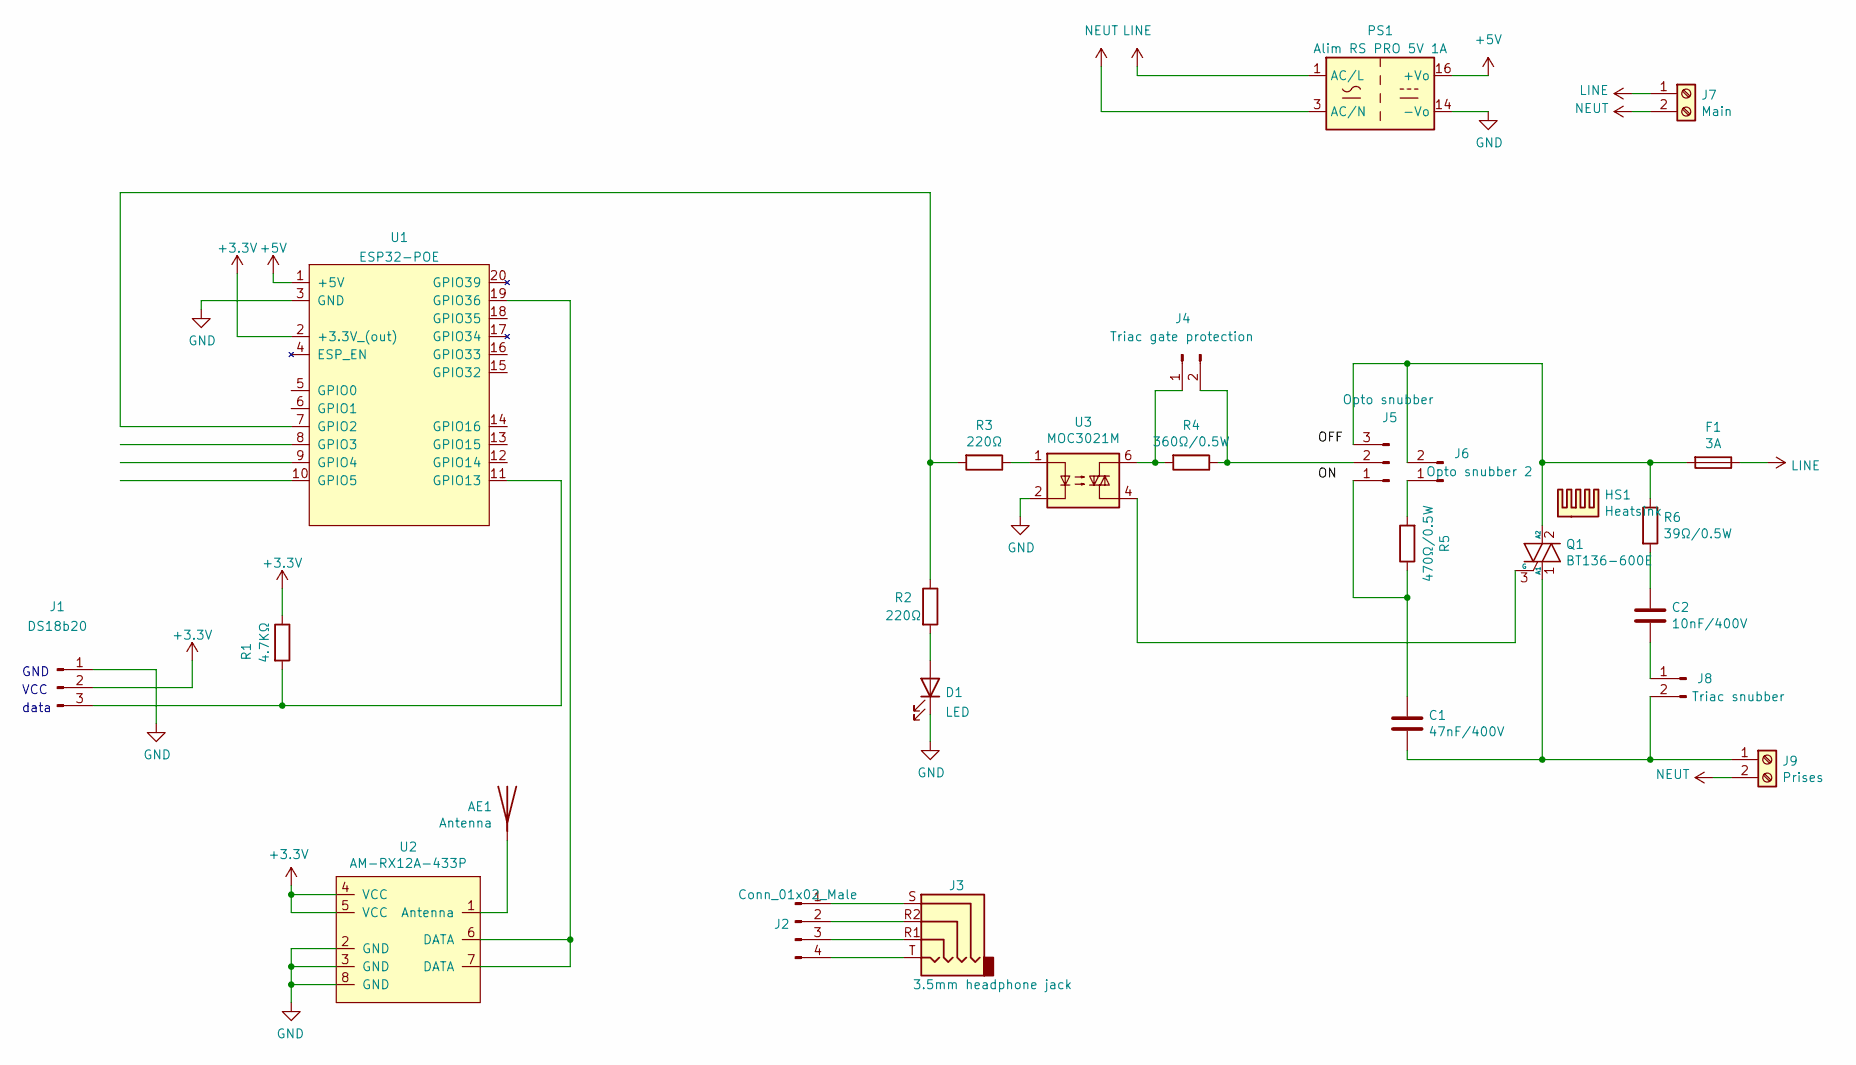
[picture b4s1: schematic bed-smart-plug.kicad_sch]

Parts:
AE1: Antenna; PinHeader_1x01_P2.54mm_Vertical
C1: 47nF/400V; C_1206_3216Metric; LCSC C309031
C2: 10nF/400V; C_0805_2012Metric; LCSC C106840
D1: LED; D_0805_2012Metric; LCSC C2297
F1: 3A; Fuseholder_Cylinder-5x20mm_Schurter_0031_8201_Horizontal_Op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
HS1: Heatsink; Heatsink_Fischer_SK104-STC-STIC_35x13mm_2xDrill2.5mm
J1: DS18b20; PinHeader_1x03_P2.54mm_Vertical
J2: Conn_01x02_Male; PinHeader_1x04_P2.54mm_Vertical
J3: 3.5mm headphone jack; Jack_3.5mm_PJ320D_Horizontal; LCSC C521460
J4: Triac gate protection; PinHeader_1x02_P2.54mm_Vertical
J5: Opto snubber; PinHeader_1x03_P2.54mm_Vertical
J6: Opto snubber 2; PinHeader_1x02_P2.54mm_Vertical
J7: Main; TerminalBlock_bornier-2_P5.08mm
J8: Triac snubber; PinHeader_1x02_P2.54mm_Vertical
J9: Prises; TerminalBlock_bornier-2_P5.08mm
PS1: Alim RS PRO 5V 1A; Converter_ACDC_MeanWell_IRM-03-xx_THT
Q1: BT136-600E; TO-220-3_Vertical
R1: 4.7KΩ; R_0402_1005Metric; LCSC C25900
R2, R3: 220Ω; R_0603_1608Metric; LCSC C22962
R4: 360Ω/0.5W; R_1210_3225Metric; LCSC C2759574
R5: 470Ω/0.5W; R_1210_3225Metric; LCSC C830186
R6: 39Ω/0.5W; R_1210_3225Metric; LCSC C422307
U1: ESP32-POE
U2: AM-RX12A-433P; AMRX12A433P
U3: MOC3021M; SMDIP-6_W9.53mm; LCSC C108500

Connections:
+3V3: J1.2, R1.1, U1.2 (+3.3V_(out)), U2.4 (VCC), U2.5 (VCC)
+5V: PS1.16 (+Vo), U1.1 (+5V)
GND: D1.1 (K), J1.1, PS1.14 (-Vo), U1.3 (GND), U2.2 (GND), U2.3 (GND), U2.8 (GND), U3.2
LINE: F1.1, J7.1, PS1.1 (AC/L)
NEUT: J7.2, J9.2, PS1.3 (AC/N)
unnamed: AE1.1 (A), U2.1 (Antenna)
unnamed: C2.1, R6.2
unnamed: D1.2 (A), R2.2
unnamed: J1.3, R1.2, U1.11 (GPIO13)
unnamed: J2.1, J3.S
unnamed: J2.2, J3.R2
unnamed: J2.3, J3.R1
unnamed: J2.4, J3.T
unnamed: J4.1, R4.2, U3.6
unnamed: J4.2, J5.2, R4.1
unnamed: C1.1, J5.1, R5.1
unnamed: F1.2, J5.3, J6.2, Q1.2 (A2), R6.1
unnamed: J6.1, R5.2
unnamed: C2.2, J8.1
unnamed: C1.2, J8.2, J9.1, Q1.1 (A1)
unnamed: Q1.3 (G), U3.4
unnamed: R3.1, U3.1
unnamed: R2.1, R3.2, U1.7 (GPIO2)
unnamed: U1.19 (GPIO36), U2.6 (DATA), U2.7 (DATA)

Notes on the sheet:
VCC
data
GND
